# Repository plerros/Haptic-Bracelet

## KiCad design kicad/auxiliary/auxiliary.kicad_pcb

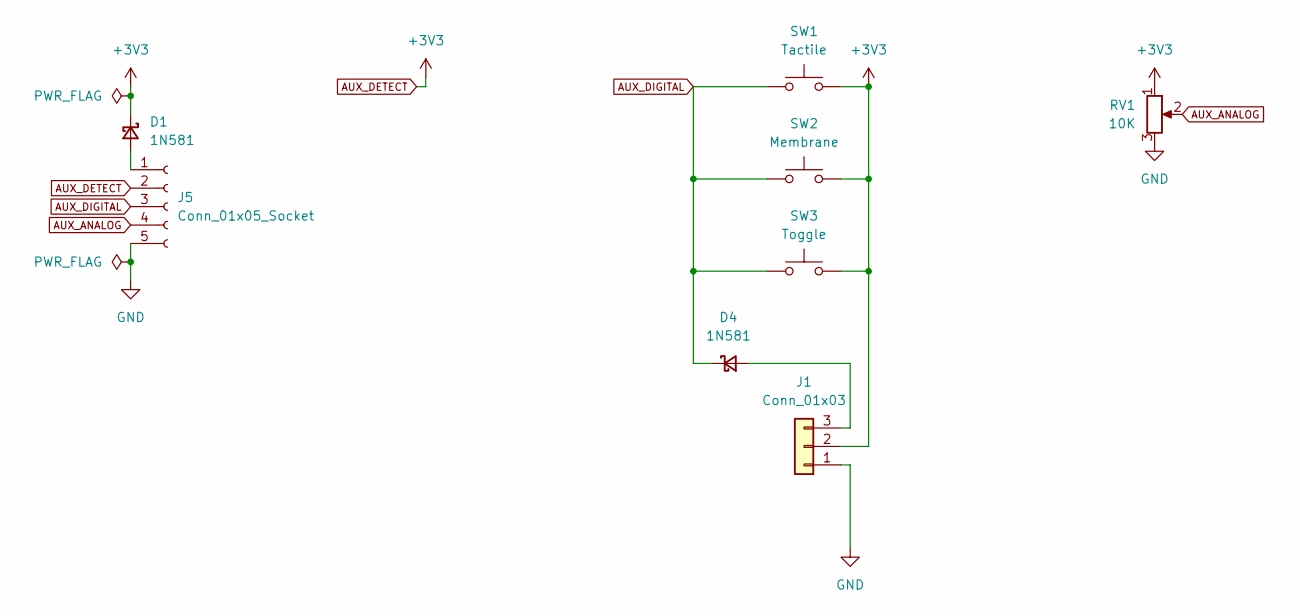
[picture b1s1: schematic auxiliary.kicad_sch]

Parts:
D1, D4: 1N581; D_A-405_P10.16mm_Horizontal
J1: Conn_01x03; PCB
J5: Conn_01x05_Socket; JST_PH_S5B-PH-K_1x05_P2.00mm_Horizontal
RV1: 10K; Potentiometer_Piher_PC-16_Single_Horizontal
SW1: Tactile; SW_PUSH_6mm
SW2: Membrane; SW_PUSH_8.5mm
SW3: Toggle; SW_Push_2P2T_Toggle_CK_PVA2OAH5xxxxxxV2

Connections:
AUX_ANALOG: J5.4, RV1.2
AUX_DETECT: D1.1 (K), J1.2, J5.2, RV1.1, SW1.2, SW2.2, SW3.2
AUX_DIGITAL: D4.1 (K), J5.3, SW1.1, SW2.1, SW3.1
GND: J1.1, J5.5, RV1.3
unnamed: D1.2 (A), J5.1
unnamed: D4.2 (A), J1.3

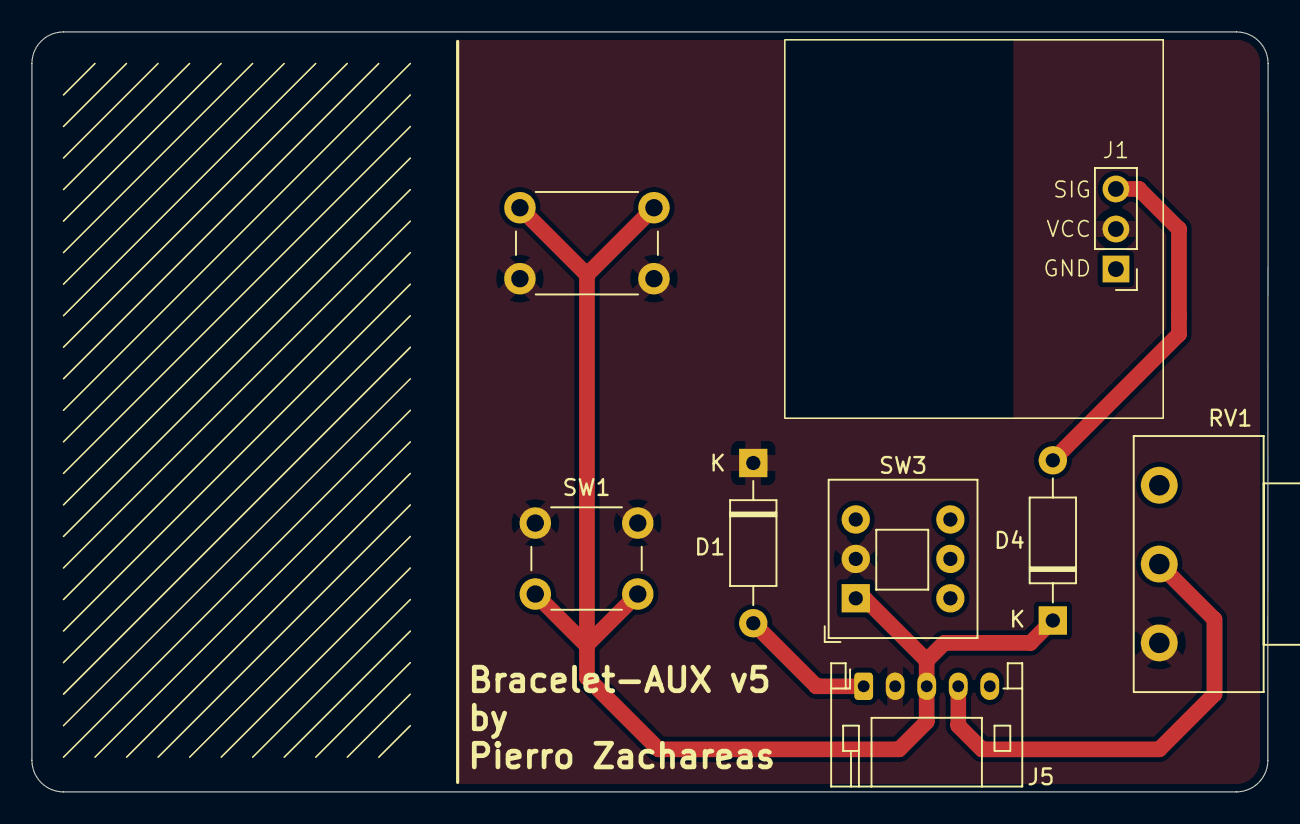
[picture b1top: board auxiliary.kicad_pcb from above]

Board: 2 copper layers, 78.4 x 48.2 mm, 8 parts (0 on the bottom side), 6 nets.

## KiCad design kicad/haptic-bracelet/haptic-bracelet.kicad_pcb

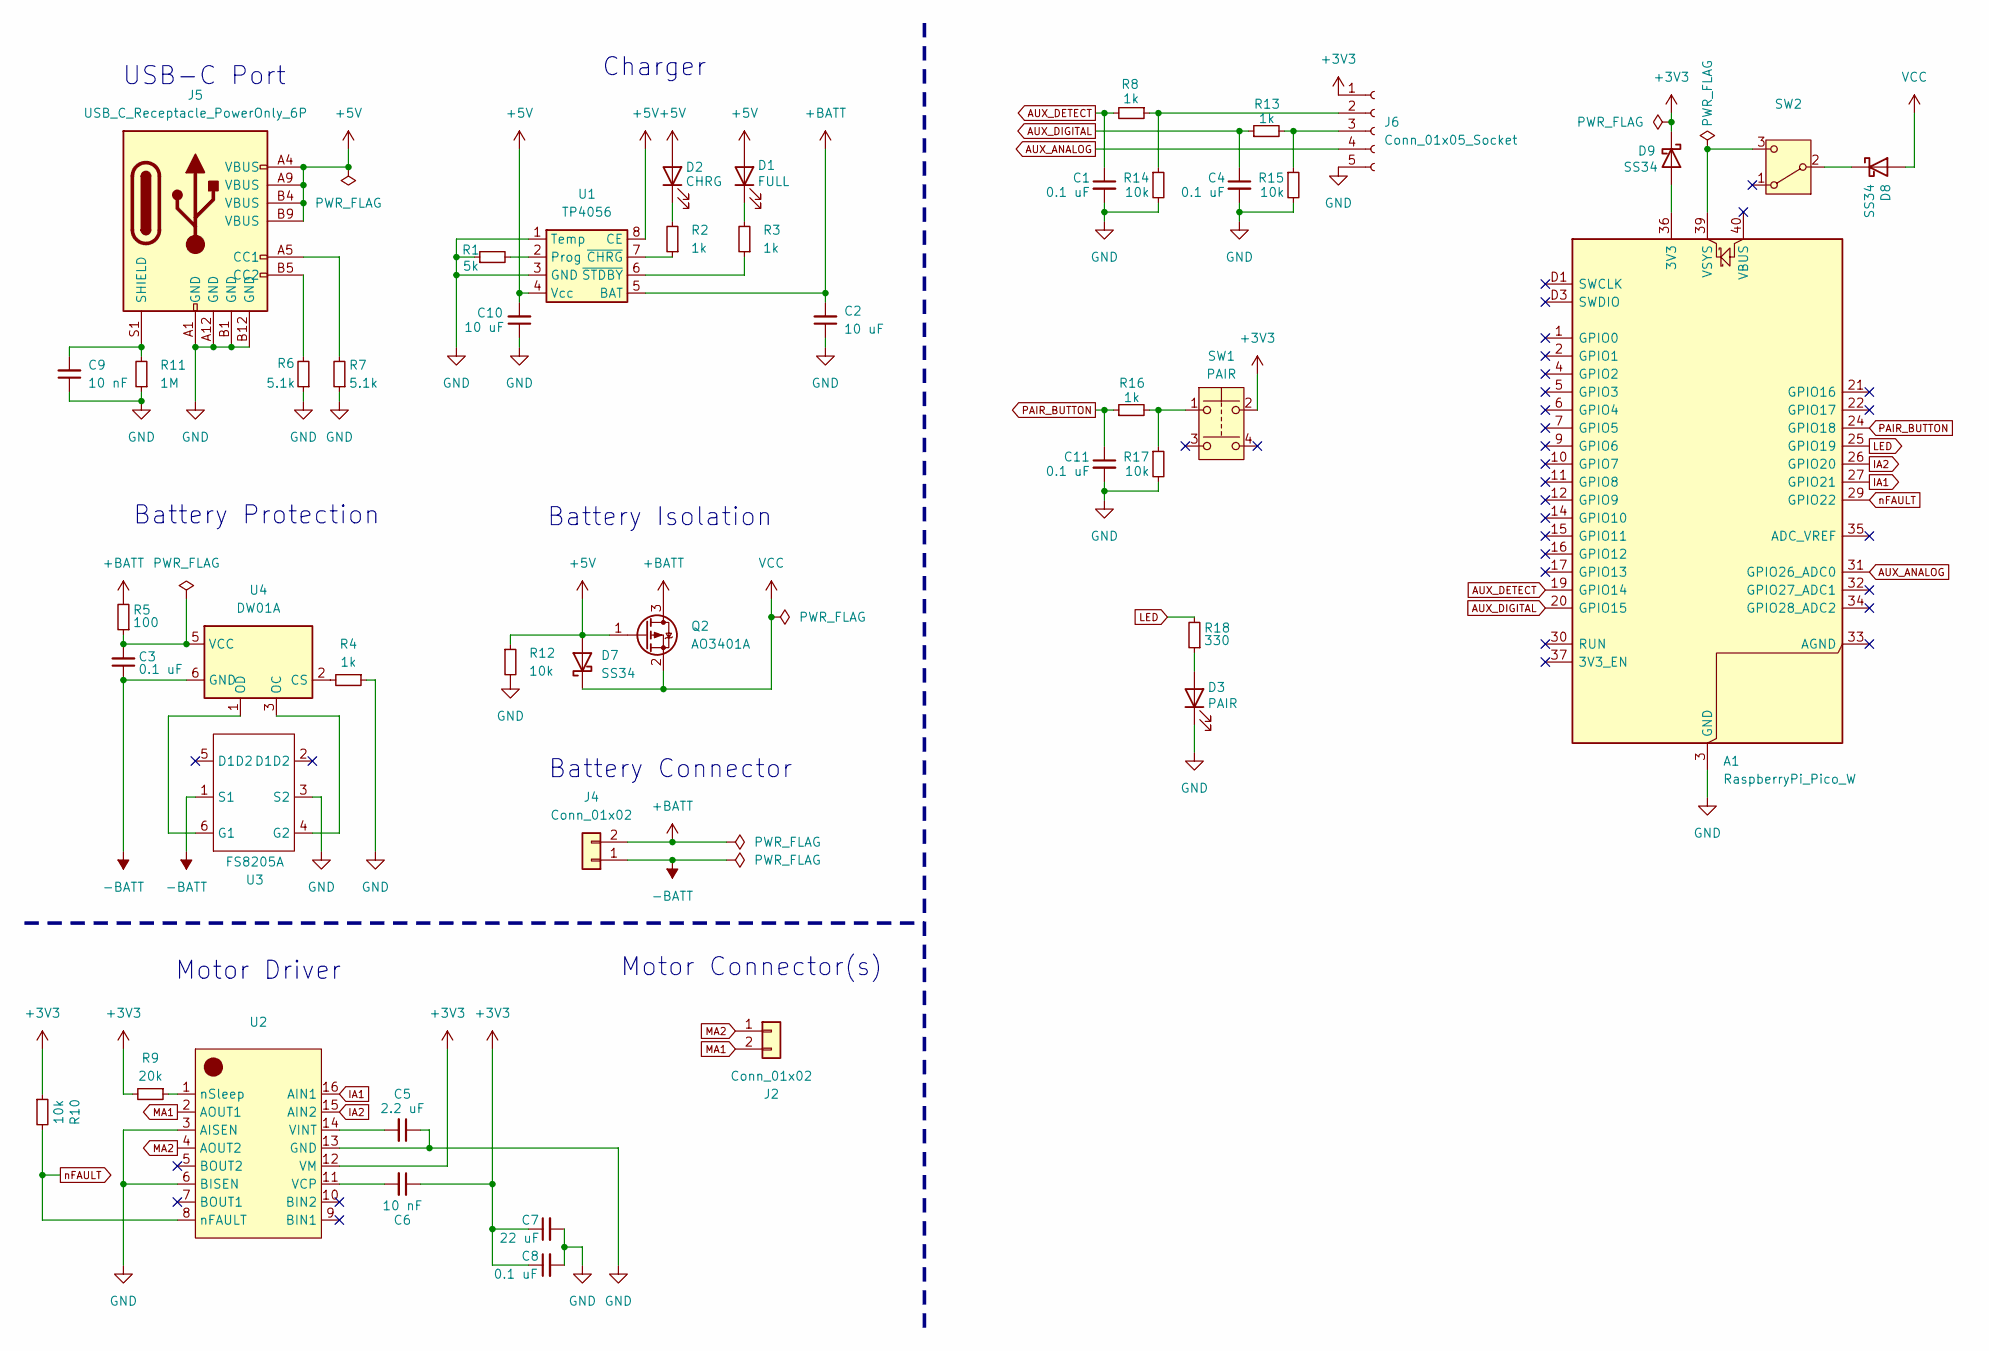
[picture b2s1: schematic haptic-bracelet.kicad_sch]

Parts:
A1: RaspberryPi_Pico_W; RaspberryPi_Pico_Common_THT
C1, C3, C4, C8, C11: 0.1 uF; C_0603_1608Metric; LCSC C1525
C2, C10: 10 uF; C_0402_1005Metric; LCSC C15525
C5: 2.2 uF; C_0402_1005Metric; LCSC C12530
C6, C9: 10 nF; C_0402_1005Metric; LCSC C15195
C7: 22 uF; C_0402_1005Metric; LCSC C415703
D1: FULL; LED_0805_2012Metric; LCSC C5569446
D2: CHRG; LED_0603_1608Metric; LCSC C5357909
D3: PAIR; LED_0603_1608Metric; LCSC C193191
D7, D8, D9: SS34; D_SMA; LCSC C8678
J2, J4: Conn_01x02; JST_SH_SM02B-SRSS-TB_1x02-1MP_P1.00mm_Horizontal; LCSC C160402
J5: USB_C_Receptacle_PowerOnly_6P; USB_C_Receptacle_HCTL_HC-TYPE-C-16P-01A; LCSC C2765186
J6: Conn_01x05_Socket; JST_SH_SM05B-SRSS-TB_1x05-1MP_P1.00mm_Horizontal; LCSC C3029344
Q2: AO3401A; SOT-23; LCSC C15127
R1: 5k; R_0402_1005Metric; LCSC C477765
R2, R3, R4, R8, R13, R16: 1k; R_0402_1005Metric; LCSC C11702
R5: 100; R_0402_1005Metric; LCSC C25076
R6, R7: 5.1k; R_0402_1005Metric; LCSC C25905
R9: 20k; R_0402_1005Metric; LCSC C25765
R10, R12, R14, R15, R17: 10k; R_0402_1005Metric; LCSC C25744
R11: 1M; R_0402_1005Metric; LCSC C26083
R18: 330; R_0402_1005Metric; LCSC C23138
SW1: PAIR; SW_Push_1P1T_XKB_TS-1187A; LCSC C318884
SW2: SW_SPDT; SW_SPDT_PCM12 vertical; LCSC C3008584
U1: TP4056; Texas_HTSOP-8-1EP_3.9x4.9mm_P1.27mm_EP2.95x4.9mm_Mask2.4x3.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; LCSC C7473158
U2: TSSOP-16-1EP_4.4x5mm_P0.65mm_EP3x3mm_ThermalVias; LCSC C128666
U3: FS8205A; SOT-23-6; LCSC C908265
U4: DW01A; SOT-23-6; LCSC C2927799

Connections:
+3V3: C6.1, C7.1, C8.1, D9.1 (K), J6.1, R9.2, R10.1, SW1.2, U2.12 (VM)
+5V: C10.2, D1.2 (A), D2.2 (A), D7.2 (A), J5.A4 (VBUS), J5.A9 (VBUS), J5.B4 (VBUS), J5.B9 (VBUS), Q2.1 (G), R12.1, U1.4 (Vcc), U1.8 (CE)
+BATT: C2.2, J4.2, Q2.3 (D), R5.2, U1.5 (BAT)
-BATT: C3.1, J4.1, U3.1 (S1), U4.6 (GND)
AUX_ANALOG: A1.31 (GPIO26_ADC0), J6.4
AUX_DETECT: A1.19 (GPIO14), C1.1, R8.2
AUX_DIGITAL: A1.20 (GPIO15), C4.1, R13.1
GND: A1.3 (GND), A1.8 (GND), A1.13 (GND), A1.18 (GND), A1.23 (GND), A1.28 (GND), A1.38 (GND), A1.D2 (GND), C1.2, C2.1, C4.2, C5.1, C7.2, C8.2, C9.1, C10.1, C11.2, D3.1 (K), J5.A1 (GND), J5.A12 (GND), J5.B1 (GND), J5.B12 (GND), J6.5, R1.1, R4.1, R6.1, R7.1, R11.1, R12.2, R14.2, R15.2, R17.2, U1.1 (Temp), U1.3 (GND), U2.3 (AISEN), U2.6 (BISEN), U2.13 (GND), U3.3 (S2)
IA1: A1.27 (GPIO21), U2.16 (AIN1)
IA2: A1.26 (GPIO20), U2.15 (AIN2)
LED: A1.25 (GPIO19), R18.2
MA1: J2.2, U2.2 (AOUT1)
MA2: J2.1, U2.4 (AOUT2)
unnamed: A1.36 (3V3), D9.2 (A)
unnamed: A1.39 (VSYS), SW2.3 (C)
unnamed: D1.1 (K), R3.2
unnamed: D2.1 (K), R2.2
unnamed: D3.2 (A), R18.1
unnamed: D8.1 (K), SW2.2 (B)
unnamed: J5.A5 (CC1), R7.2
unnamed: J5.B5 (CC2), R6.2
unnamed: C9.2, J5.S1 (SHIELD), R11.2
unnamed: J6.2, R8.1, R14.1
unnamed: J6.3, R13.2, R15.1
unnamed: R16.2, R17.1, SW1.1
unnamed: R1.2, U1.2 (Prog)
unnamed: R2.1, U1.7 (~CHRG)
unnamed: R3.1, U1.6 (~STDBY)
unnamed: C6.2, U2.11 (VCP)
unnamed: C5.2, U2.14 (VINT)
unnamed: R9.1, U2.1 (nSleep)
unnamed: U3.6 (G1), U4.1 (OD)
unnamed: U3.4 (G2), U4.3 (OC)
unnamed: R4.2, U4.2 (CS)
unnamed: C3.2, R5.1, U4.5 (VCC)
PAIR_BUTTON: A1.24 (GPIO18), C11.1, R16.1
VCC: D7.1 (K), D8.2 (A), Q2.2 (S)
nFAULT: A1.29 (GPIO22), R10.2, U2.8 (nFAULT)

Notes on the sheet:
USB-C Port
Charger
Battery Protection
Motor Driver
Battery Connector
Motor Connector(s)
Battery Isolation

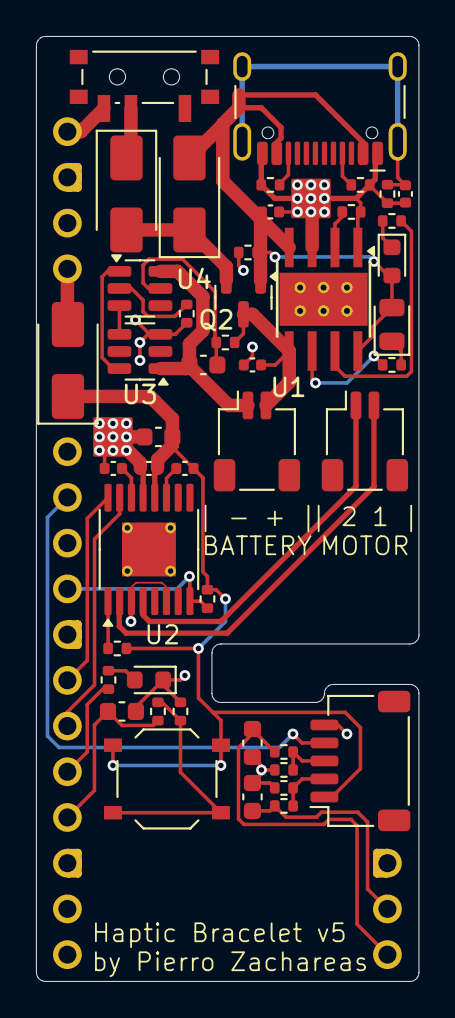
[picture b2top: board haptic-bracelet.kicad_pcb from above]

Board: 2 copper layers, 21.3 x 52.5 mm, 47 parts (1 on the bottom side), 38 nets.

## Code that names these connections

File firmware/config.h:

/*
 * Copyright (c) 2025 Pierro Zachareas
 *
 * SPDX-License-Identifier: GPL-3.0-only
 */

#ifndef HAPTIC_BRACELET_CONFIG_H
#define HAPTIC_BRACELET_CONFIG_H

#include <stdbool.h>

// Pins
#define PIN_LED         19
#define PIN_PAIR        18

#define PIN_MOTOR_A1    21
#define PIN_MOTOR_A2    20
#define PIN_MOTOR_FAULT 22

#define PIN_AUX_DETECT  14
#define PIN_AUX_DIGITAL 15
#define PIN_AUX_ANALOG  26

#define ADC_CHANNEL_AUX_ANALOG 0

/*
 * PRINTF
 *
 * Can be either: 'printf' or 'nanoprintf'
 */
#define PRINTF printf

#define ANALOG_AVERAGING_WINDOW 64

#define MEASURE_CALLBACK_TIME false

#endif /* HAPTIC_BRACELET_CONFIG_H */

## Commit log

2025-03-25 initial calibration & tests
2025-03-28 hardware updates on timer
    no need to manually call update()
2025-03-28 workaround to enable LTO
    - included nanoprintf library
2025-04-08 move main
2025-04-08 led driver
2025-04-11 functional aux board
2025-04-11 analog measurement averaging
2025-04-16 npf enable long format
2025-04-16 reduce analog update
    added a sliding window that keeps previous analog values and takes the average, instead of making 64 reads on each update
    used to take 160-350 μs, now takes 8 μs
2025-04-16 even faster callback time
    store the sum and conditionally subtract the old value and add the new one
    reduces time from 8 μs to 5 μs
2025-04-16 vibrate when letting go of button
2025-04-16 don't interrupt an active pulse
2025-04-18 add npf interface
    - can use `nanoprintf()` from multiple source files
2025-04-18 initial ble code
    It just does bluetooth le pairing.
    cy43 can't be compiled with -flto because of printf warnings
2025-04-18 haptic tuning
    - 2nd activation to analog potentiometer
    - feedback dampening in motor
2025-04-23 blink led on pair
2025-04-29 bt debug messages
2025-04-29 keep running
    Don't end execution if everything else finishes.
2025-04-29 initial code for BLE unpair
2025-06-26 switch to bt classic + fixes
    - using rfcomm over bt classic
    - switched to atomic on some variables
2025-07-06 unity scripts
2025-09-05 kicad files
2025-09-05 freecad files
